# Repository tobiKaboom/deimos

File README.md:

# Δεῖμος
Deimos is a 40% split unibody ortholinear keyboard that uses the Raspberry Pi Pico for more accessibility, whose layout is similiar to the Lesovoz but has easier kitting. 

## Parts list
| Part          | Specifics     | Amount |
| ------------- | ------------- | ------ |
| Diodes        | DO-35 THT diodes (part number 1N4148)  | 38     |
| Switches      | MX standard switches  | 37     |
| Board         | Raspberry Pi Pico (classic board) | 1      |
| Buttons | 6mm micro-switches | 2 |
| LED | 5mm LED | 2 |
| Electrical tape | - | 1 |
| Resistor | 220 ohm | 1 |
## Tools list
| Tools         | Is it necessary? | Use |
| ------------- | ------------- | ------ |
| Soldering iron      | Yes  | Soldering |
| Solder wire| Yes | Soldering |
| Screwdriver | Yes | Screwing in standoffs |
| Tape | No, but reccomended | Holding components in place |
| Tweezers | No, but reccomended | Placing smaller parts |
| Fan or solder hood | No, but reccomended | Safety |
| Eye protection | No, but reccomended | Safety |

## Firmware 
Deimos currently runs on KMK. If you want to try and port it to QMK, ZMK or any other firmware you are welcome to do so.

## License
This work falls under the Creative Commons Attribution-ShareAlike 4.0 international license.
For more info, check LICENSE.md or https://creativecommons.org/licenses/by-sa/4.0/deed.en

## Issues
The right button is supposed to light up the LED, but it will burn it out. I am dumb. Use a resistor to avoid that.

## Disclaimer
This PCB has been fully tested and confirmed to work. The members of the PCB development team are however not liable if you end up with a non-functional pcb. Order at your own risk. Support will not be provided but pull requests will be reviewed and possibly accepted, although i do not know how that works.

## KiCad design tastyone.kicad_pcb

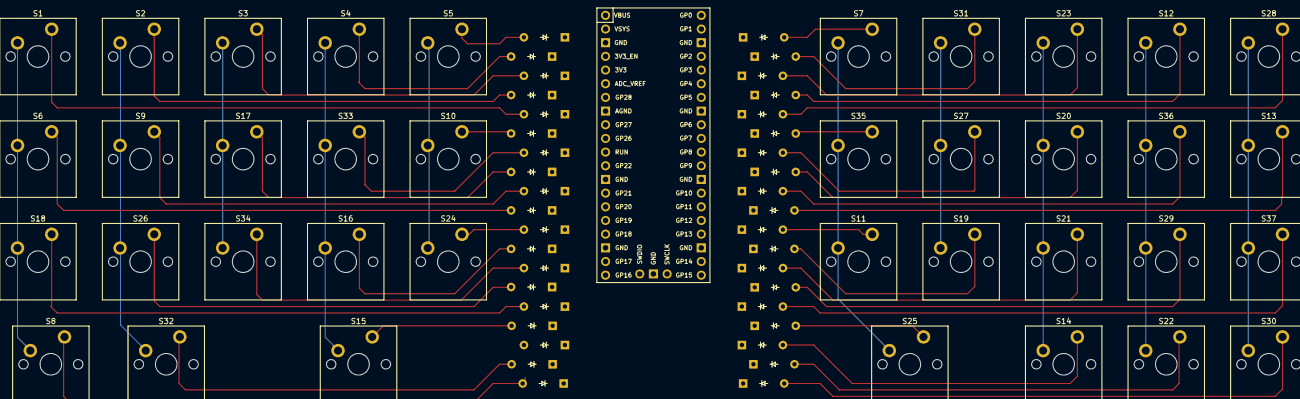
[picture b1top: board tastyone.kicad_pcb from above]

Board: 2 copper layers, 76 parts (1 on the bottom side), 32 nets.

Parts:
D1, D1#2, D2, D2#2, D3, D3#2, D4, D4#2, D5, D5#2, D6, D6#2, D7, D7#2, D8, D8#2, D9, D9#2, D10, D10#2, D11, D11#2, D11#3, D11#4, D12, D12#2, D13, D13#2, D14, D14#2, D15, D15#2, D16, D16#2, D17, D17#2, D18, D18#2: Diode; DO-35
S1, S2, S3, S4, S5, S6, S7, S9, S10, S11, S12, S13, S14, S16, S17, S18, S19, S20, S21, S22, S23, S24, S26, S27, S28, S29, S30, S31, S32, S33, S34, S35, S36, S37: Keyswitch; MX_PCB_1.00u
S8: Keyswitch; MX_PCB_1.25u
S15: Keyswitch; MX_PCB_2.75u
S25: Keyswitch; MX_PCB_2.00u
U1: Raspberry_Pi_Pico

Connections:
C0: S1.1, S2.1, S3.1, S4.1, U1.1 (GPIO0)
C1: S5.1, S6.1, S7.1, S8.1, U1.2 (GPIO1)
C2: S9.1, S10.1, S11.1, U1.4 (GPIO2)
C3: S12.1, S13.1, S14.1, S15.1, U1.5 (GPIO3)
C4: S16.1, S17.1, S18.1, U1.6 (GPIO4)
C5: S19.1, S20.1, S21.1, U1.7 (GPIO5)
C6: S22.1, S23.1, S24.1, S25.1, U1.9 (GPIO6)
C7: S26.1, S27.1, S28.1, S29.1, U1.10 (GPIO7)
C8: S30.1, S31.1, S32.1, S33.1, U1.11 (GPIO8)
C9: S34.1, S35.1, S36.1, S37.1, U1.12 (GPIO9)
unnamed: D1.2 (A), D1#2.2 (A), S1.2
unnamed: D2.2 (A), D2#2.2 (A), S2.2
unnamed: D3.2 (A), D3#2.2 (A), S3.2
unnamed: D4.2 (A), D4#2.2 (A), S4.2
unnamed: D5.2 (A), D5#2.2 (A), S5.2
unnamed: D6.2 (A), D6#2.2 (A), S6.2
unnamed: D7.2 (A), D7#2.2 (A), S7.2
unnamed: D8.2 (A), D8#2.2 (A), S8.2
unnamed: D9.2 (A), D9#2.2 (A), S9.2
unnamed: D10.2 (A), D10#2.2 (A), S10.2
unnamed: D11.2 (A), D11#2.2 (A), D11#3.2 (A), D11#4.2 (A), S11.2
unnamed: D12.2 (A), D12#2.2 (A), S12.2
unnamed: D13.2 (A), D13#2.2 (A), S13.2
unnamed: D14.2 (A), D14#2.2 (A), S14.2
unnamed: D15.2 (A), D15#2.2 (A), S15.2
unnamed: D16.2 (A), D16#2.2 (A), S16.2
unnamed: D17.2 (A), D17#2.2 (A), S17.2
unnamed: D18.2 (A), D18#2.2 (A), S18.2
R0: D1.1 (K), D1#2.1 (K), D5.1 (K), D5#2.1 (K), D9.1 (K), D9#2.1 (K), D12.1 (K), D12#2.1 (K), D16.1 (K), D16#2.1 (K), U1.14 (GPIO10), U1.41 (SWCLK), U1.42 (GND), U1.43 (SWDIO)
R1: D2.1 (K), D2#2.1 (K), D6.1 (K), D6#2.1 (K), D10.1 (K), D10#2.1 (K), D13.1 (K), D13#2.1 (K), D17.1 (K), D17#2.1 (K), U1.15 (GPIO11)
R2: D3.1 (K), D3#2.1 (K), D7.1 (K), D7#2.1 (K), D11.1 (K), D11#2.1 (K), D11#3.1 (K), D11#4.1 (K), D14.1 (K), D14#2.1 (K), D18.1 (K), D18#2.1 (K), U1.16 (GPIO12)
R3: D4.1 (K), D4#2.1 (K), D8.1 (K), D8#2.1 (K), D15.1 (K), D15#2.1 (K), U1.17 (GPIO13)

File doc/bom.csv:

Designator,Footprint,Quantity,Value,LCSC Part #
"D1_2, D1, D10_2, D10, D11_4, D11_3, D11_2, D11, D12_2, D12, D13_2, D13, D14_2, D14, D15_2, D15, D16_2, D16, D17_2, D17, D18_2, D18, D2_2, D2, D3_2, D3, D4_2, D4, D5_2, D5, D6_2, D6, D7_2, D7, D8_2, D8, D9_2, D9",DO-35,38,Diode,
"S1, S10, S11, S12, S13, S14, S16, S17, S18, S19, S2, S20, S21, S22, S23, S24, S26, S27, S28, S29, S3, S30, S31, S32, S33, S34, S35, S36, S37, S4, S5, S6, S7, S9",MX_PCB_1.00u,34,Keyswitch,
S15,MX_PCB_2.75u,1,Keyswitch,
S25,MX_PCB_2.00u,1,Keyswitch,
S8,MX_PCB_1.25u,1,Keyswitch,
U1,Raspberry_Pi_Pico,1,Raspberry_Pi_Pico,

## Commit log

2024-05-15 Create noone
2024-05-21 Create LICENSE
2024-05-28 Create a
2024-05-28 Create aaaaaa
2024-05-28 Create production
2024-05-28 Create partslist
2024-05-28 Create deimosfm
2024-05-28 Update deimosfm
2024-05-28 Update partslist
2024-06-02 Rename deinosplate.stl to deimosplate.stl
2024-06-08 Update LICENSE
2024-06-08 Rename LICENSE to LICENSE.md
2024-06-08 Create test,md
2024-06-09 Rename deimosfm to deimosfm_kmk
2024-06-09 Create deimosfm_rpk
2024-06-09 Update deimosfm_kmk
2024-06-09 Rename deimosfm_kmk to deimosfm_kmk.py
2025-01-18 fixed typo
2025-03-20 added keeb pic
2025-03-20 changed image source
